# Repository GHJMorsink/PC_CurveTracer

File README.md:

# PC_CurveTracer

*Curve tracing for bjt transistors, FETs, diodes and more through ATMega micro and PC*

## Introduction

This project builds an I-V Curve Tracer connected to a computer using USB. A curve tracer is a type of instrument used to 
measure the current through a device with varying voltages across it. It is a specialized piece of electronic test equipment 
to analyze the characteristics of discrete electronic components, such as diodes, and transistors. The device contains 
voltage and current sources that can be used to stimulate the device under test (DUT). The curve tracer applies a continuously 
varying voltage to two terminals of the device under test and measure the amount of current that the device permits to flow 
at each voltage. This so-called I-V (current versus voltage) data is directly displayed on an oscilloscope screen in X-Y mode.
Examples of full featured Curve tracers which can go to more than 100 Volt and currents into several amps are the Textronix 576, 577, 
and the Leader LTC-905. Simpler (and cheaper) solutions are based on a simple transformer with a few resistors like 
in [Changpuak's curvetracer](https://www.changpuak.ch/electronics/Curve_Tracer_advanced.php). All of these need an oscilloscope 
as the display device.
This project builds one which does not use an oscilloscope, but shows the data, and the controls on a computer. The interface 
to the computer is through USB, and the power is also taken from the USB connection. This means the device can only handle 
signal-sized discrete components up to 5 Volt and a maximum of about 10 mAmpere.

## Hardware

The hardware used is based on a simple microcontroller (good old Atmel ATMega8) which generates the varying voltages with two PWM-DAC based outputs. 
The measurements are done with the internal ADC. For switching between NPN and PNP transistors (or N-mosfets and P-mosfets) one 
of the digital outputs is used.
The USB connection is based on the V-USB package of OBDev [V-USB](https://github.com/obdev/v-usb).
The power section for the DUT contains an opamp for buffering the DAC output, so it can sink and source currents. The resistor 
measures the current and creates at the same time a current limiting function. The second opamp is arranged as a current to 
voltage convertor with some gain so that about 10 mA gives a full scale for the ADC. Note that the ground reference for the 
floating current convertor is switched to accommodate for positive and negative currents. Also be aware the opamps inputs 
and outputs must reach rail to rail voltages. The control connection for the DUT (the base, or the gate) has fairly simple set-up 
from the second PWM-DAC with one RC-filter and a high value resistor; FETs get a voltage, bipolar transistors get a small current.

## Firmware

To be able to connect to the device without needing a software driver, the system will work as a HID device. Communication will 
be on the features report channel. The device and the used protocol has the capacity for 16 different modes with each 8 functions. 
At the moment only the mode for measuring a trace and resetting (for firmware updates) are implemented. The functions are 
initializing, reading measurements, and reading and setting calibration data. More modes and funtions can be created in the 
future; there is still enough room on an ATMega8. One can think of an automated hFE measurement mode and likewise modes for FETs.
Creating one trace is done by the initializing command containing the info for the used bias voltage (and this determines 
directly the bias current in cases of bipolar transistors), the number of measurement points, and the polarity to be used. 
After the initialization the requested number of measurements can be retrieved. There are also commands for setting and reading 
calibration values, which are needed for correction of the current to voltage conversion. The calibration is used at PC 
software level, and stored on the device because it is 'attached' to the components of that device.

The firmware contains a hid-based usb bootloader. This helps in a simple system where updates of the firmware can be transported 
conveniently to the device. The software supports this mechanism (it was used heavily during development).

## Software

The controlling GUI is built using a Python script. The graphics are made using the PyQT and pyqtgraph packages. The connection 
with the device is through USB using the pywinusb package. Starting the GUI through main.py gives the following window:

It defaults to top-right quadrant for 5 traces, good for a normal npn transistor.

Within the application it is possible to update the firmware, so new features can be introduced. There is also a bootload.py 
script which gives the possibility to update the firmware or give it the initial firmware using the console.

## Results and calibration

Connecting the hardware to the computer, and starting the software conveniently through the CurveTracer.bat file gives the 
opportunity to calibrate it. This calibration is necessary only once. Put a 1kOhm resistor (1%) in the hardware between the collector 
and emitter pins, and do a 'single shot' measurement. You should see a straight line through points 0mA/0V,  1mA/1V,  2mA/2V, and 3mA/3V. 
If the line isn't correct, you can adjust it by changing the 'Current correction voltage', 'Set' it, and do a new measurement.

A view of some other measurements are in the next pictures. A LED, a pnp transistor (BC213) and a npn transistor (2SC945). The last 
one in full graph mode: you get a single trace in the opposite quadrant, without any base/gate stimulation.

Note: You can right-click on the graph for saving the picture and other goodies, supplied out of the box from the pyqtgraph package.

## Tooling and other notes

The hardware is developed with a somewhat older version of CadSoft's EAGLE pcb design software, now part of Autodesk Fusion Software.
Version 7.5.0 was used. For reference the schematic and the pcb design are also given as pdf document.
The firmware is written using the Microchip Studio 7.0 environment. You can get it through the URL [https://www.microchip.com/en-us/tools-resources](https://www.microchip.com/en-us/tools-resources/develop/microchip-studio#Downloads); older Atmel versions will work as well. 
The firmware is with minor or no changes also usable on the ATMega88 and the bigger ATMega168 and ATMega328. The fuse settings 
for the microcontroller can be found in the document [Fuses.txt](./embedded/fuses.txt).
For convenience a hex file containing the image for the application and the bootloader is in the file ./embedded/full.hex.
The PC software is fully based o Python. Version 3.12 was used during development, any version in the 3-series should be fine. 
The requirements.txt contains the names of the needed packages to conveniently install them using 'pip'. For users who want to 
adapt/develop the software to their likings, it is advised to install QT Designer as well.

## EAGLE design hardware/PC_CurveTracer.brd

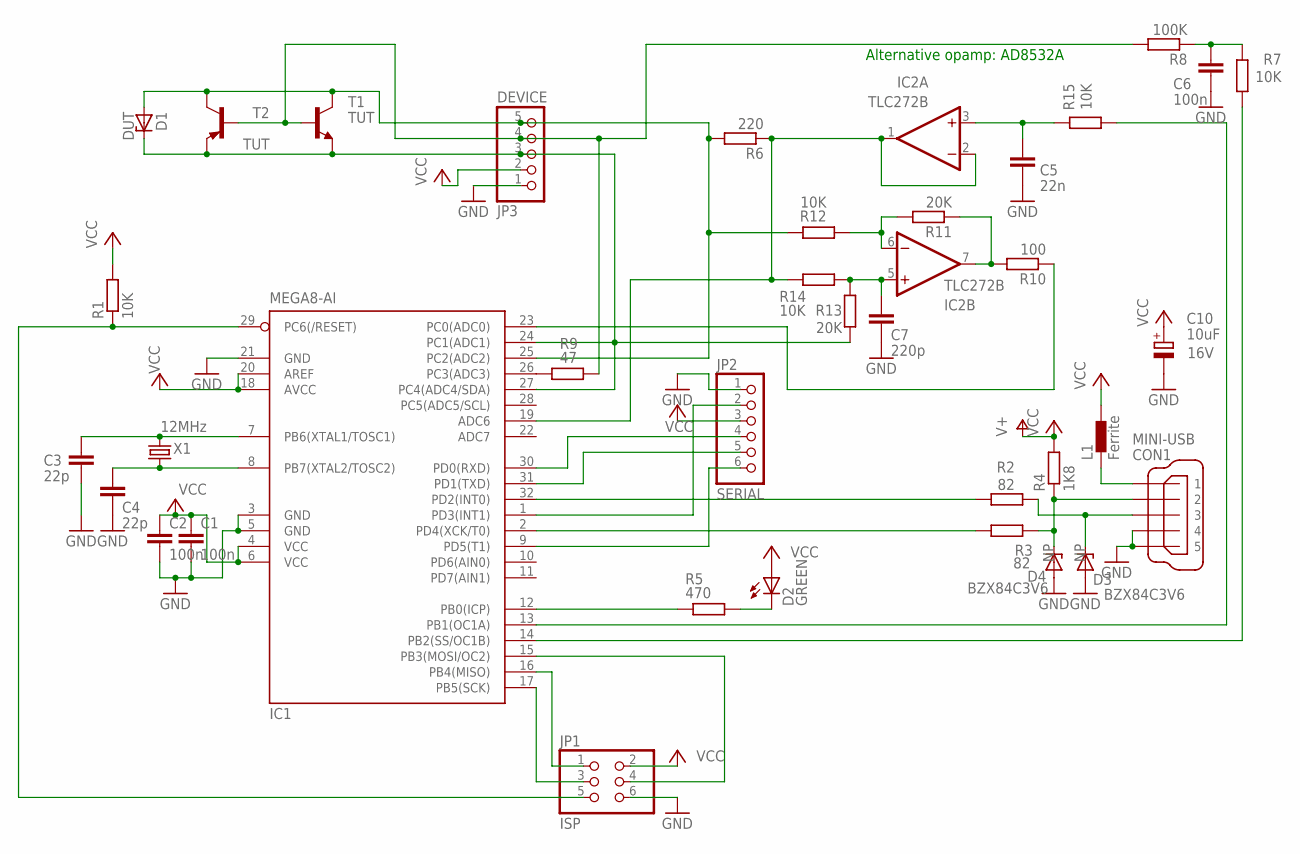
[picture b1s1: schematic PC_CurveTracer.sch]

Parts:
C1, C2, C6: 100n; C1206
C3, C4: 22p; C0603
C5: 22n; C1206
C7: 220p; C1206
C10: 10uF; SMC_C; VOLTAGE 16V
CON1: MINI-USB; 32005-400
D1: DUT; SOD80C
D2: GREEN; SML0805
D3, D4: BZX84C3V6; TO236
IC1: MEGA8-AI; TQFP32-08
IC2: TLC272B; SO08
JP1: ISP; 2X03
JP2: SERIAL; 1X06
JP3: DEVICE; 1X05
L1: Ferrite; 0402
R1, R7, R12, R14, R15: 10K; R1206
R2, R3: 82; R1206
R4: 1K8; R1206
R5: 470; R1206
R6: 220; R1206
R8: 100K; R1206
R9: 47; R1206
R10: 100; R1206
R11, R13: 20K; R1206
T1: TUT; SOT23
T2: TUT; SOT89-ECB
X1: 12MHz; HC49/S

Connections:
GND: C1.2, C2.2, C3.2, C4.2, C5.2, C6.2, C7.2, C10.-, CON1.4, CON1.5, D3.A, D4.A, IC1.3 (GND), IC1.5 (GND), IC1.21 (GND), IC2.4 (GND), JP1.6, JP2.1, JP3.1
unnamed: IC1.29 (PC6(/RESET)), JP1.5, R1.1
unnamed: D2.C, R5.1
unnamed: C3.1, IC1.7 (PB6(XTAL1/TOSC1)), X1.2
unnamed: C4.1, IC1.8 (PB7(XTAL2/TOSC2)), X1.1
unnamed: IC1.16 (PB4(MISO)), JP1.1
unnamed: CON1.1, L1.1
unnamed: IC1.15 (PB3(MOSI/OC2)), JP1.4
unnamed: IC1.12 (PB0(ICP)), R5.2
unnamed: IC1.32 (PD2(INT0)), R2.2
unnamed: IC1.1 (PD3(INT1)), JP2.2
unnamed: CON1.3, D3.C, R2.1
unnamed: IC1.30 (PD0(RXD)), JP2.4
unnamed: IC1.2 (PD4(XCK/T0)), R3.2
unnamed: CON1.2, D4.C, R3.1, R4.1
unnamed: IC1.13 (PB1(OC1A)), R15.1
unnamed: C6.1, R7.2, R8.1
unnamed: IC2.6 (-IN), R11.2, R12.1
unnamed: IC1.31 (PD1(TXD)), JP2.5
unnamed: D1.C, IC1.24 (PC1(ADC1)), IC1.27 (PC4(ADC4/SDA)), JP3.3, R13.1, T1.2 (E), T2.E
unnamed: IC1.9 (PD5(T1)), JP2.6
unnamed: IC1.23 (PC0(ADC0)), R10.1
unnamed: IC1.26 (PC3(ADC3)), R9.1
unnamed: IC1.19 (ADC6), IC2.1 (OUT), IC2.2 (-IN), R6.1, R14.2
unnamed: IC2.7 (OUT), R10.2, R11.1
unnamed: IC1.14 (PB2(SS/OC1B)), R7.1
unnamed: D1.A, IC1.25 (PC2(ADC2)), JP3.5, R6.2, R12.2, T1.3 (C), T2.C
unnamed: C7.1, IC2.5 (+IN), R13.2, R14.1
unnamed: IC1.17 (PB5(SCK)), JP1.3
unnamed: C5.1, IC2.3 (+IN), R15.2
TUT: JP3.4, R8.2, R9.2, T1.1 (B), T2.B
VCC: C1.1, C2.1, C10.+, D2.A, IC1.4 (VCC), IC1.6 (VCC), IC1.18 (AVCC), IC1.20 (AREF), IC2.8 (VCC), JP1.2, JP2.3, JP3.2, L1.2, R1.2, R4.2

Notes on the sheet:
Alternative opamp: AD8532A

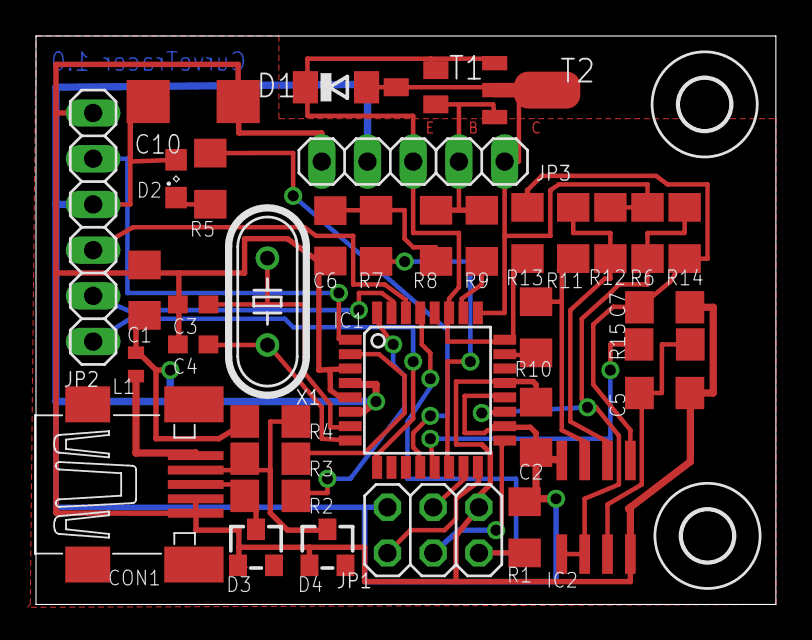
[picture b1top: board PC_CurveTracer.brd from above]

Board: 2 copper layers, 41.1 x 31.6 mm, 39 parts (0 on the bottom side), 32 nets.

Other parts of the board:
HOLE1, HOLE2: -; 2,8

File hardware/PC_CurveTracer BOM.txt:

Partlist exported from D:/projects/PC_CurveTracer/hardware/PC_CurveTracer.sch at 06/05/2025 17:49

Part Value     Device                       Package   Description                                MF MPN          NP OC_FARNELL OC_NEWARK VOLTAGE
C1   100n      C-EUC1206                    C1206     CAPACITOR, European symbol                                                                
C2   100n      C-EUC1206                    C1206     CAPACITOR, European symbol                                                                
C3   22p       C-EUC0603                    C0603     CAPACITOR, European symbol                                                                
C4   22p       C-EUC0603                    C0603     CAPACITOR, European symbol                                                                
C5   22n       C-EUC1206                    C1206     CAPACITOR, European symbol                                                                
C6   100n      C-EUC1206                    C1206     CAPACITOR, European symbol                                                                
C7   220p      C-EUC1206                    C1206     CAPACITOR, European symbol                                                                
C10  10uF      CPOL-EUSMCC                  SMC_C     POLARIZED CAPACITOR, European symbol                                               16V    
CON1 MINI-USB  MINI-USB_SHIELD5P4-32005-400 32005-400 MINI USB-B R/A W/O POST 5 pol.                                unknown    unknown          
D1   DUT       ZENER-DIODESOD80C            SOD80C    Z-Diode                                                                                   
D2   GREEN     LEDSML0805                   SML0805   LED                                                                                       
D3   BZX84C3V6 BZX84CSMD                    TO236     Z DIODE                                                    NP                             
D4   BZX84C3V6 BZX84CSMD                    TO236     Z DIODE                                                    NP                             
IC1  MEGA8-AI  MEGA8-AI                     TQFP32-08 MICROCONTROLLER                               ATMEGA8-16AU    9171371    73M8863          
IC2  TLC272B   LM358D                       SO08      OP AMP also LM158; LM258; LM2904                                                          
JP1  ISP       PINHD-2X3                    2X03      PIN HEADER                                                                                
JP2  SERIAL    PINHD-1X6                    1X06      PIN HEADER                                                                                
JP3  DEVICE    PINHD-1X5                    1X05      PIN HEADER                                                                                
L1   Ferrite   BLM15HG601SN1                0402      EMIFIL (R) Chip Ferrite Bead for GHz Noise                                                
R1   10K       R-EU_R1206                   R1206     RESISTOR, European symbol                                                                 
R2   82        R-EU_R1206                   R1206     RESISTOR, European symbol                                                                 
R3   82        R-EU_R1206                   R1206     RESISTOR, European symbol                                                                 
R4   1K8       R-EU_R1206                   R1206     RESISTOR, European symbol                                                                 
R5   470       R-EU_R1206                   R1206     RESISTOR, European symbol                                                                 
R6   220       R-EU_R1206                   R1206     RESISTOR, European symbol                                                                 
R7   10K       R-EU_R1206                   R1206     RESISTOR, European symbol                                                                 
R8   100K      R-EU_R1206                   R1206     RESISTOR, European symbol                                                                 
R9   47        R-EU_R1206                   R1206     RESISTOR, European symbol                                                                 
R10  100       R-EU_R1206                   R1206     RESISTOR, European symbol                                                                 
R11  20K       R-EU_R1206                   R1206     RESISTOR, European symbol                                                                 
R12  10K       R-EU_R1206                   R1206     RESISTOR, European symbol                                                                 
R13  20K       R-EU_R1206                   R1206     RESISTOR, European symbol                                                                 
R14  10K       R-EU_R1206                   R1206     RESISTOR, European symbol                                                                 
R15  10K       R-EU_R1206                   R1206     RESISTOR, European symbol                                                                 
T1   TUT       BC846                        SOT23     NPN TRANSISTOR                                                                            
T2   TUT       -PNP-SOT89-ECB               SOT89-ECB PNP Transistror                                                                           
X1   12MHz     CRYSTALHC49S                 HC49/S    CRYSTAL                                                       1667008    unknown

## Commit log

2025-05-12 Publishing
2025-10-27 Adding generation file for PyInstaller executable
